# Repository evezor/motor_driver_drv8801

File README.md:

# Motor Driver DRV8801 

*please note this board is has been deprecated.

This board uses the Evezor Stamp STMF405 MCU

source: https://github.com/evezor/Evezor-Stamp-STMF405

An edge board with 2, 36 Volt, 2.8A max DRV8801 motor drivers

Evezor® and all associated marks, logos, and designs are registered trademarks and protected by copyright. Unauthorized use or reproduction of these trademarks and copyrighted materials is strictly prohibited.
.

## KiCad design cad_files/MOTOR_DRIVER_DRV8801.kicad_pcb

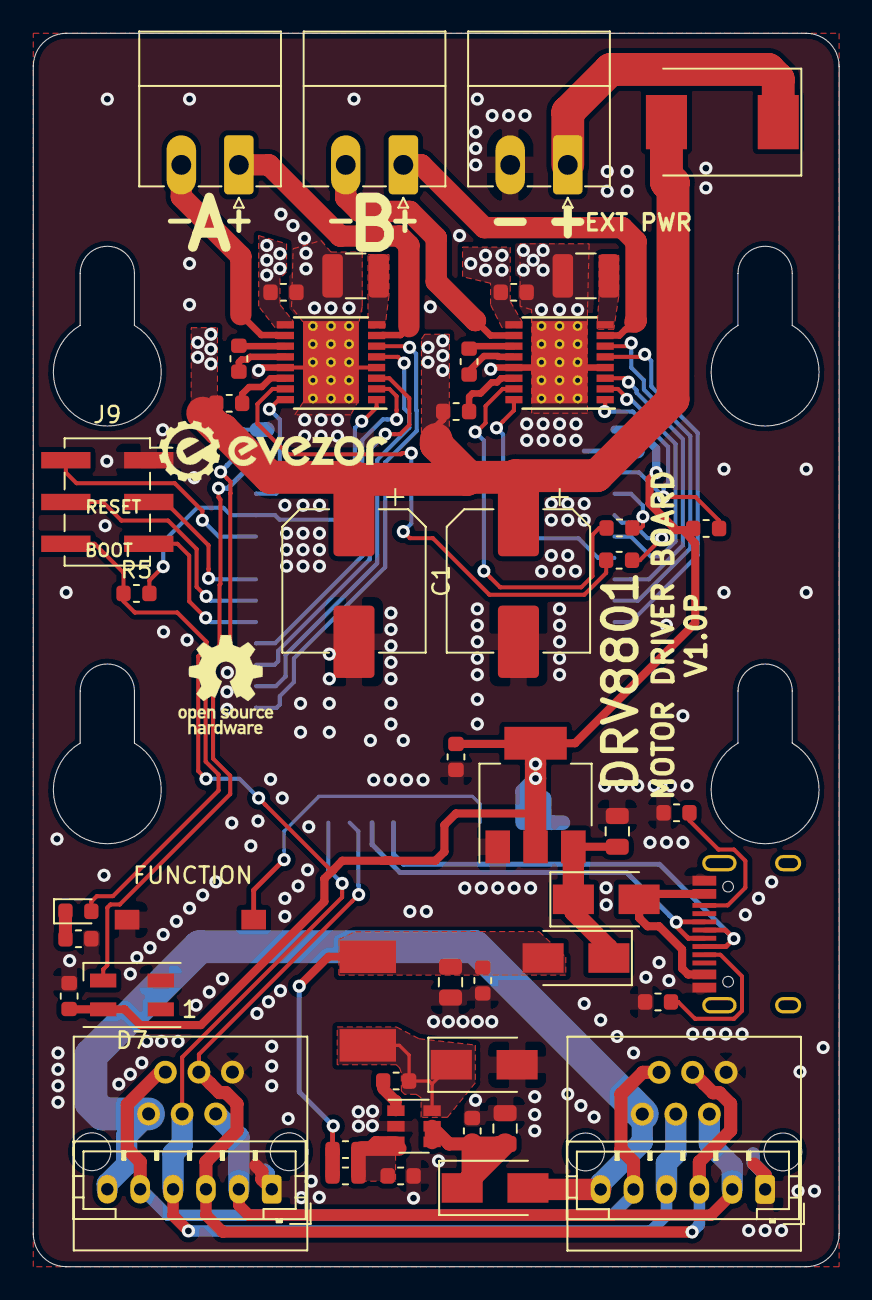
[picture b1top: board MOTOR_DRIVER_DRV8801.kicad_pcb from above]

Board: 2 copper layers, 49.0 x 75.0 mm, 51 parts (1 on the bottom side), 56 nets.

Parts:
C1, C2: 100uF; CP_Elec_8x10.5
C3, C4, C5, C6, C7, C8: 100nF; C_0603_1608Metric
C9, C10, C11, C13, C17: .1uF; C_0603_1608Metric
C12: 4.7uF; C_0805_2012Metric
C14: 22uF; C_0805_2012Metric
C15: 10uF; C_0805_2012Metric
C18: C_Small; C_0603_1608Metric
D1: SK86; D_SMC
D2, D3, D4, D5: SX35_SCHOTTKY; D_SMA
D6: LED; LED_0603_1608Metric
D7: SK6812MINI; LED_SK6812MINI_PLCC4_3.5x3.5mm_P1.75mm
J1, J2, J3: Conn_01x02; PhoenixContact_MC_1,5_2-G-3.5_1x02_P3.50mm_Horizontal
J4: USB_C_Receptacle_USB2.0; USB_C_Receptacle_HRO_TYPE-C-31-M-12
J5, J6: PH; JST_PH_B6B-PH-K_1x06_P2.00mm_Vertical
J7, J8: RJ11; RJ11_C189747_Horizontal
J9: Conn_02x03_Odd_Even; PinSocket_2x03_P2.54mm_Vertical_SMD
L1: 22uH; INDUCTOR_7.5X6.6_GCDA0630-220MC
R1, R2: .2; R_1210_3225Metric
R3, R4: 100k; R_0603_1608Metric
R5, R6: 10k; R_0603_1608Metric
R7, R11: 15k; R_0603_1608Metric
R8: 82k; R_0603_1608Metric
R9, R10: 5.1k; R_0603_1608Metric
SW1: SW_Push; SWITCH_2x3_SMD_TACTILE_GREEN
U1, U2: DRV8801PWP; HTSSOP-16-1EP_4.4x5mm_P0.65mm_EP3.4x5mm_Mask3x3mm_ThermalVi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
U3: SY8401ABC; SOT-23-6
U4: EDGE_STM32F405_CPU_V1; EDGE_STAMP
U5: AMS1117-3.3; SOT-223-3_TabPin2

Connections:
+3V3: C17.1, C18.2, D7.4, J9.6, R5.1, R6.1, U4.1, U4.18, U5.2
/ADC_A: R3.1, U4.5
/ADC_B: R4.1, U4.4
/BOOT: J9.3, U4.36
/CAN_H: J5.3, J6.3, J7.3, J8.3, U4.26
/CAN_L: J5.4, J6.4, J7.4, J8.4, U4.27
/CC1: J4.A5, R10.1
/CC2: J4.B5, R9.1
/D+: J4.A6, J4.B6, U4.25
/D-: J4.A7, J4.B7, U4.24
/ENABLE_A: U1.6, U4.30
/ENABLE_B: U2.6, U4.9
/FAULT_A: R5.2, U1.1, U4.39
/FAULT_B: R6.2, U2.1, U4.3
/FD_H: J5.2, J6.2, J7.2, J8.2
/FD_L: J5.5, J6.5, J7.5, J8.5
/FUNCTION_BUTTON: SW1.1, U4.20
/HBT_LED: D6.2, U4.41
/MODE_1_A: U1.2, U4.33
/MODE_1_B: U2.2, U4.6
/MODE_2_A: U1.16, U4.40
/MODE_2_B: U2.16, U4.7
/NEO_STATUS: D7.3, U4.42
/OLED_SCL: J9.5, U4.34
/OLED_SDA: J9.4, U4.35
/PHASE_A: U1.3, U4.32
/PHASE_B: U2.3, U4.8
/RESET: J9.2, U4.38
/SLEEP_A: U1.5, U4.31
/SLEEP_B: U2.5, U4.10
/USB_VCC: D4.2, J4.A4, J4.A9, J4.B4, J4.B9
/VREG_OUT: C10.1, C13.1, C14.1, D5.2, L1.2, R8.1
GND: C1.2, C2.2, C7.2, C8.2, C11.2, C12.2, C13.2, C14.2, C15.2, C17.2, C18.1, D2.2, D7.2, J3.2, J4.A1, J4.A12, J4.B1, J4.B12, J5.1, J6.1, J7.1, J8.1, J9.1, R1.1, R2.1, R7.1, R9.2, R10.2, R11.1, SW1.2, U1.4, U1.13, U1.17, U2.4, U2.13, U2.17, U3.2, U4.2, U4.17, U4.43, U5.1
unnamed: C3.2, U1.14
unnamed: C4.2, U2.14
unnamed: C5.1, U1.11
unnamed: C5.2, U1.12
unnamed: C6.1, U2.11
unnamed: C6.2, U2.12
unnamed: C9.1, D2.1, L1.1, U3.6
unnamed: C9.2, U3.1
unnamed: C10.2, R7.2, R8.2, U3.3
unnamed: C11.1, C12.1, D3.1, U3.4, U3.5
unnamed: C15.1, D4.1, D5.1, U5.3
unnamed: D1.1, J3.1
unnamed: D6.1, R11.2
unnamed: J1.1, U1.7
unnamed: J1.2, U1.10
unnamed: J2.1, U2.7
unnamed: J2.2, U2.10
unnamed: R1.2, U1.8
unnamed: R2.2, U2.8
unnamed: R3.2, U1.15
unnamed: R4.2, U2.15
VBUS: D3.2, J5.6, J6.6, J7.6, J8.6
Vdrive: C1.1, C2.1, C3.1, C4.1, C7.1, C8.1, D1.2, U1.9, U2.9

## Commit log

2021-04-26 add testcode
2023-09-11 Create LICENSE
2023-09-11 add pics
